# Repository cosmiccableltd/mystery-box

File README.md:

# Mystery Box

## About
The Mystery Box is a small PCB which provides power ports for various devices to indicate a ringing phone and drive POE devices.
It was designed by [Cosmic Cable Ltd.](http://cosmic.cable.limited) to be used for self-made telephone booths. 

## Ports
| Port Name | Function                                                      | Usage                                   |
| --------- | --------                                                      | -----                                   |
| J1        | [POE](https://en.wikipedia.org/wiki/Power_over_Ethernet) Port | POE powered network device              |
| J2        | LAN Port                                                      | Connection to external network          |
| J3        | Analogue Telephone Port                                       | Connection to external analogue network |
| J4        | Analogue Telephone Port                                       | Connection to analogue telephone        |
| X1-1      | +12V                                                          |                                         |
| X1-2      |  GND (switched)                                               | swichted on ringing phone line          |
| X1-3      | +12V                                                          |                                         |
| X1-4      |  GND                                                          |                                         |
| X1-5      | +12V                                                          |                                         |
| X1-6      |  GND                                                          |                                         |
| X1-7      | +12V                                                          |                                         |
| X1-8      |  GND                                                          |                                         |

## Known Issues
We experienced that the PMV20EN Q2 Mosfet might die from to high current.
It should be changed to something which can handle more current or otherwise it must be ensured that the outgoing power is limited.

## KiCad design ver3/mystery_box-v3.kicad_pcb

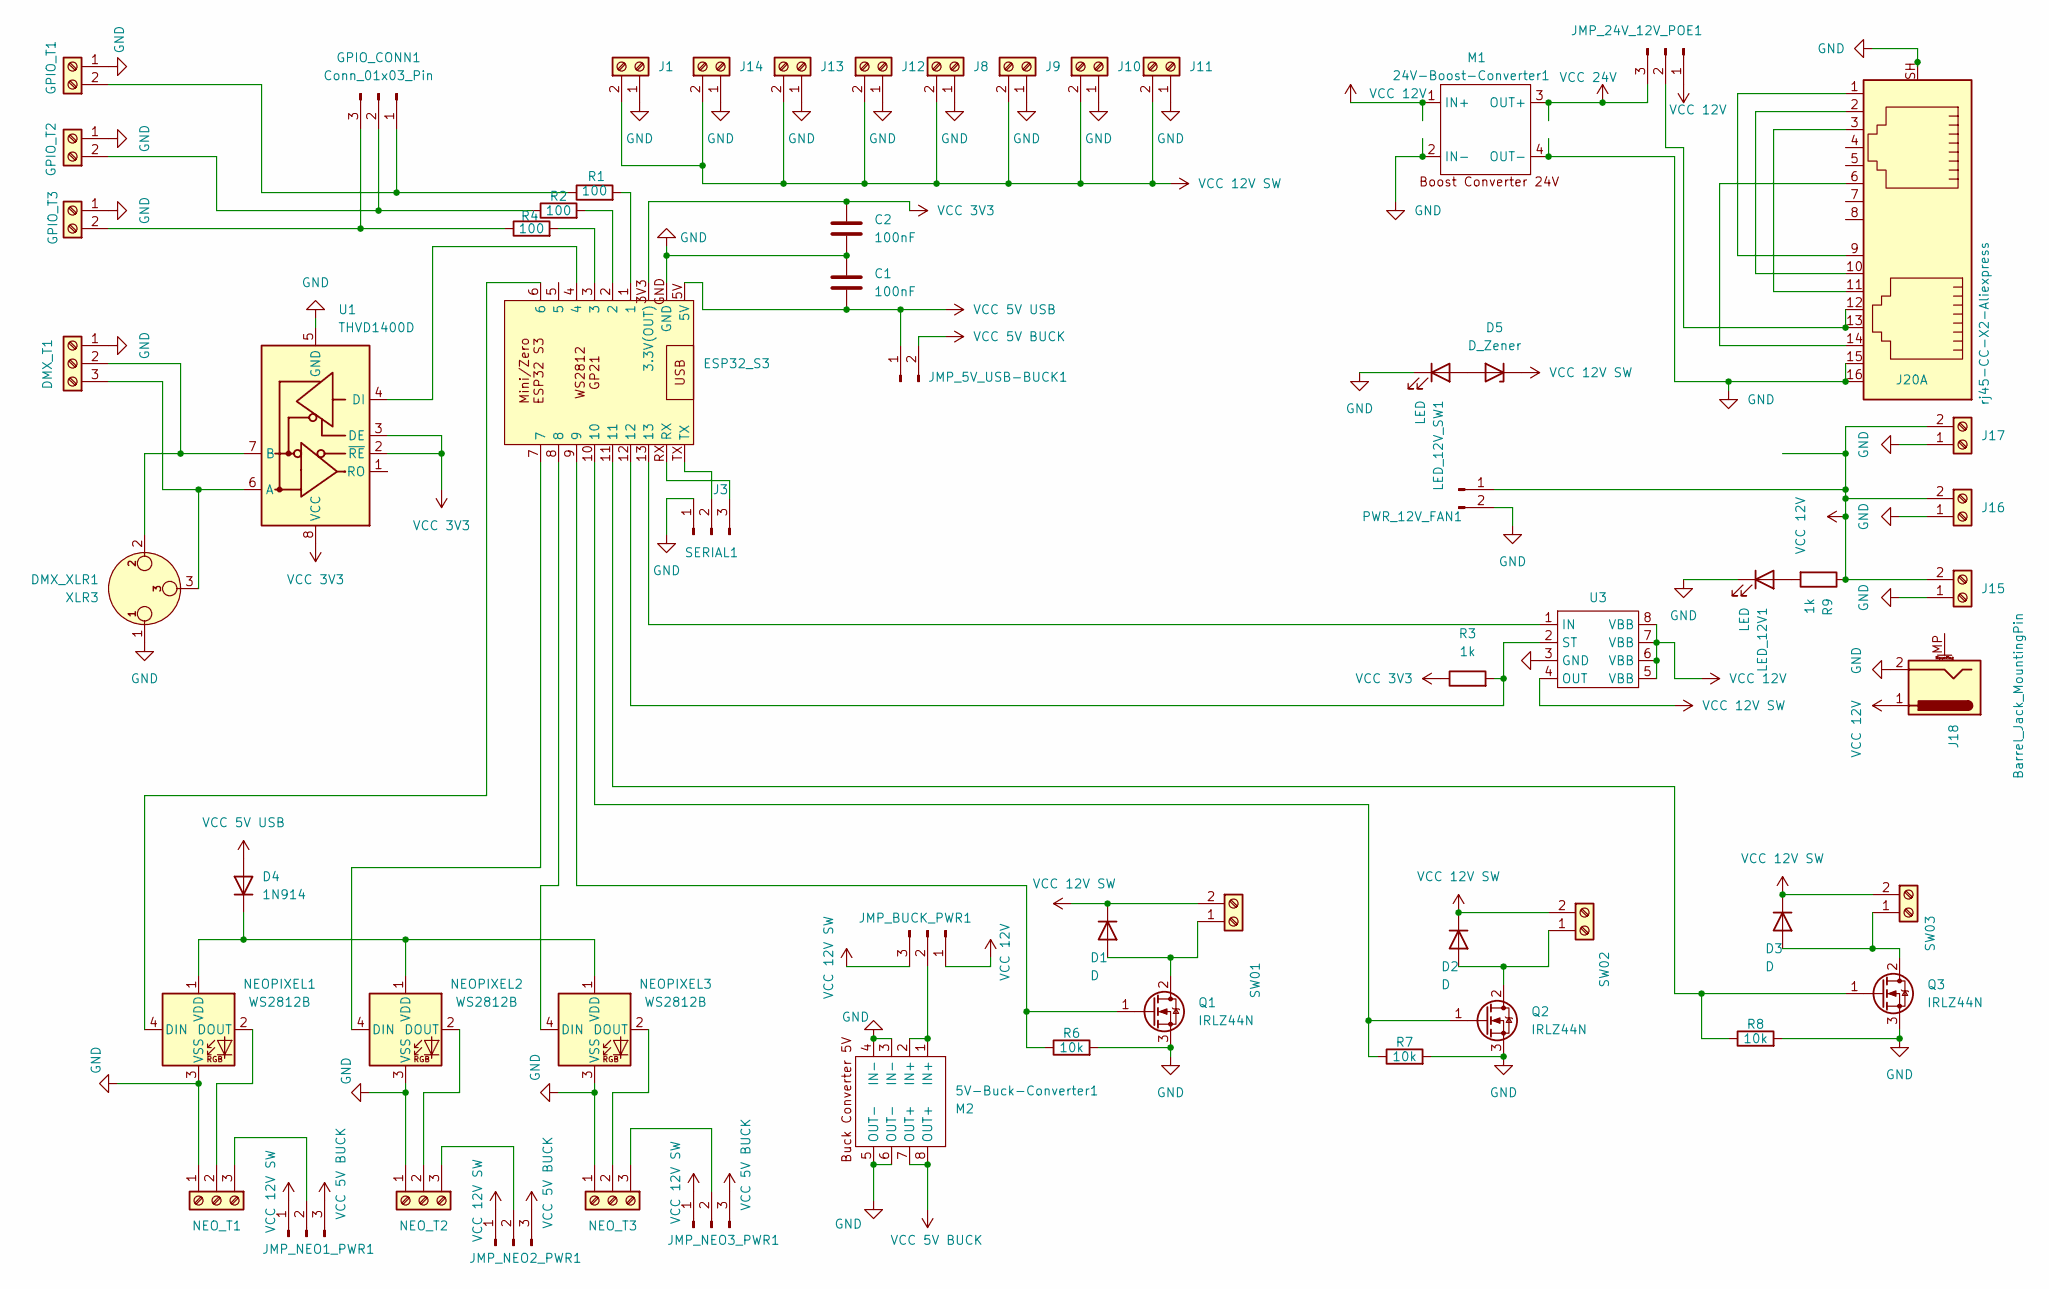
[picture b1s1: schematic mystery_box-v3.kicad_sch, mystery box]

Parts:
5V-Buck-Converter1: M2; 5V Buck Converter
24V-Boost-Converter1: M1; 24V Boost Converter
C1, C2: 100nF; C_Rect_L7.0mm_W2.5mm_P5.00mm
D1, D2, D3: D; D_DO-15_P10.16mm_Horizontal
D4: 1N914; D_DO-35_SOD27_P7.62mm_Horizontal
D5: D_Zener; D_A-405_P7.62mm_Horizontal
DMX_T1: Screw_Terminal_01x03; TerminalBlock_MaiXu_MX126-5.0-03P_1x03_P5.00mm
DMX_XLR1: XLR3; Jack_XLR_Neutrik_NC3FAAH-0_Horizontal
ESP32_S3: ESP32-S3-Zero
GPIO_CONN1: Conn_01x03_Pin; PinHeader_1x03_P2.54mm_Vertical
GPIO_T1, GPIO_T2, GPIO_T3: Screw_Terminal_01x02; TerminalBlock_MaiXu_MX126-5.0-02P_1x02_P5.00mm
J1, J8, J9, J10, J11, J12, J13, J14, J15, J16, J17: Screw_Terminal_01x02; TerminalBlock_MaiXu_MX126-5.0-02P_1x02_P5.00mm
J3: SERIAL1; PinHeader_1x03_P2.54mm_Vertical
J18: Barrel_Jack_MountingPin; CUI_PJ-050BH
J20: rj45-CC-X2-Aliexpress; RJ45_X2_CC_Aliexpress
JMP_5V_USB-BUCK1: Conn_01x02_Pin; PinHeader_1x02_P2.54mm_Vertical
JMP_24V_12V_POE1: Conn_01x03_Pin; PinHeader_1x03_P2.54mm_Vertical
JMP_BUCK_PWR1: Conn_01x03_Pin; PinHeader_1x03_P2.54mm_Vertical
JMP_NEO1_PWR1, JMP_NEO2_PWR1, JMP_NEO3_PWR1: Conn_01x03_Pin; PinHeader_1x03_P2.54mm_Vertical
LED_12V1, LED_12V_SW1: LED; LED_D3.0mm_Horizontal_O1.27mm_Z2.0mm_Clear
NEOPIXEL1, NEOPIXEL2, NEOPIXEL3: WS2812B; LED_WS2812B_PLCC4_5.0x5.0mm_P3.2mm
NEO_T1, NEO_T2, NEO_T3: Screw_Terminal_01x03; TerminalBlock_MaiXu_MX126-5.0-03P_1x03_P5.00mm
PWR_12V_FAN1: Conn_01x02_Pin; PinHeader_1x02_P2.54mm_Vertical
Q1, Q2, Q3: IRLZ44N; TO-220-3_Vertical
R1, R2, R4: 100; R_Axial_DIN0207_L6.3mm_D2.5mm_P10.16mm_Horizontal
R3, R9: 1k; R_Axial_DIN0207_L6.3mm_D2.5mm_P10.16mm_Horizontal
R6, R7, R8: 10k; R_Axial_DIN0207_L6.3mm_D2.5mm_P10.16mm_Horizontal
SW01, SW02, SW03: Screw_Terminal_01x02; TerminalBlock_MaiXu_MX126-5.0-02P_1x02_P5.00mm
SmartSwitch1: U3; SOIC-8_3.9x4.9mm_P1.27mm
U1: THVD1400D; SOIC-8_3.9x4.9mm_P1.27mm

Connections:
GND: 5V-Buck-Converter1.3 (IN-), 5V-Buck-Converter1.4 (IN-), 5V-Buck-Converter1.5 (OUT-), 5V-Buck-Converter1.6 (OUT-), 24V-Boost-Converter1.2 (IN-), 24V-Boost-Converter1.4 (OUT-), C1.1, C2.2, DMX_T1.1 (Pin_3), DMX_XLR1.1, ESP32_S3.GND, GPIO_T1.1 (Pin_2), GPIO_T2.1 (Pin_2), GPIO_T3.1 (Pin_2), J1.1 (Pin_2), J3.1, J8.1 (Pin_2), J9.1 (Pin_2), J10.1 (Pin_2), J11.1 (Pin_2), J12.1 (Pin_2), J13.1 (Pin_2), J14.1 (Pin_2), J15.1 (Pin_2), J16.1 (Pin_2), J17.1 (Pin_2), J18.2, J20.15, J20.16, J20.SH, LED_12V1.1 (K), LED_12V_SW1.1 (K), NEOPIXEL1.3 (VSS), NEOPIXEL2.3 (VSS), NEOPIXEL3.3 (VSS), NEO_T1.1 (Pin_3), NEO_T2.1 (Pin_3), NEO_T3.1 (Pin_3), PWR_12V_FAN1.2, Q1.3 (S), Q2.3 (S), Q3.3 (S), R6.2, R7.2, R8.2, SmartSwitch1.3 (GND), U1.5 (GND)
unnamed: D1.2 (A), Q1.2 (D), SW01.1 (Pin_2)
unnamed: D2.2 (A), Q2.2 (D), SW02.1 (Pin_2)
unnamed: D3.2 (A), Q3.2 (D), SW03.1 (Pin_2)
unnamed: D4.1 (K), NEOPIXEL1.1 (VDD), NEOPIXEL2.1 (VDD), NEOPIXEL3.1 (VDD)
unnamed: D5.2 (A), LED_12V_SW1.2 (A)
unnamed: DMX_T1.3 (Pin_1), DMX_XLR1.3, U1.6 (A)
unnamed: DMX_T1.2, DMX_XLR1.2, U1.7 (B)
unnamed: ESP32_S3.1, R1.2
unnamed: ESP32_S3.2, R2.2
unnamed: ESP32_S3.3, R4.2
unnamed: GPIO_CONN1.1, GPIO_T1.2 (Pin_1), R1.1
unnamed: GPIO_CONN1.2, GPIO_T2.2 (Pin_1), R2.1
unnamed: GPIO_CONN1.3, GPIO_T3.2 (Pin_1), R4.1
unnamed: ESP32_S3.TX, J3.2
unnamed: ESP32_S3.RX, J3.3
unnamed: J20.1, J20.9
unnamed: J20.2, J20.10
unnamed: J20.3, J20.11
unnamed: J20.6, J20.14
unnamed 20: J20.12, J20.13, JMP_24V_12V_POE1.2; also elsewhere on the board
unnamed: 5V-Buck-Converter1.1 (IN+), 5V-Buck-Converter1.2 (IN+), JMP_BUCK_PWR1.2
unnamed: JMP_NEO1_PWR1.2, NEO_T1.3 (Pin_1)
unnamed: JMP_NEO2_PWR1.2, NEO_T2.3 (Pin_1)
unnamed: JMP_NEO3_PWR1.2, NEO_T3.3 (Pin_1)
unnamed: LED_12V1.2 (A), R9.2
unnamed: ESP32_S3.6, NEOPIXEL1.4 (DIN)
unnamed: NEOPIXEL1.2 (DOUT), NEO_T1.2
unnamed: ESP32_S3.7, NEOPIXEL2.4 (DIN)
unnamed: NEOPIXEL2.2 (DOUT), NEO_T2.2
unnamed: ESP32_S3.8, NEOPIXEL3.4 (DIN)
unnamed: NEOPIXEL3.2 (DOUT), NEO_T3.2
unnamed: ESP32_S3.9, Q1.1 (G), R6.1
unnamed: ESP32_S3.10, Q2.1 (G), R7.1
unnamed: ESP32_S3.11, Q3.1 (G), R8.1
unnamed: ESP32_S3.13, SmartSwitch1.1 (IN)
unnamed: ESP32_S3.12, R3.2, SmartSwitch1.2 (ST)
unnamed: ESP32_S3.4, U1.4 (DI)
VCC 3V3: C2.1, ESP32_S3.3V3 (3.3V(OUT)), R3.1, U1.2 (~RE), U1.3 (DE), U1.8 (VCC)
VCC 5V BUCK: 5V-Buck-Converter1.7 (OUT+), 5V-Buck-Converter1.8 (OUT+), JMP_5V_USB-BUCK1.2, JMP_NEO1_PWR1.3, JMP_NEO2_PWR1.3, JMP_NEO3_PWR1.3
VCC 5V USB: C1.2, D4.2 (A), ESP32_S3.5V, JMP_5V_USB-BUCK1.1
VCC 12V: 24V-Boost-Converter1.1 (IN+), J15.2 (Pin_1), J16.2 (Pin_1), J17.2 (Pin_1), J18.1, JMP_24V_12V_POE1.1, JMP_BUCK_PWR1.1, PWR_12V_FAN1.1, R9.1, SmartSwitch1.5 (VBB), SmartSwitch1.6 (VBB), SmartSwitch1.7 (VBB), SmartSwitch1.8 (VBB); also elsewhere on the board
VCC 12V SW: D1.1 (K), D2.1 (K), D3.1 (K), D5.1 (K), J1.2 (Pin_1), J8.2 (Pin_1), J9.2 (Pin_1), J10.2 (Pin_1), J11.2 (Pin_1), J12.2 (Pin_1), J13.2 (Pin_1), J14.2 (Pin_1), JMP_BUCK_PWR1.3, JMP_NEO1_PWR1.1, JMP_NEO2_PWR1.1, JMP_NEO3_PWR1.1, SW01.2 (Pin_1), SW02.2 (Pin_1), SW03.2 (Pin_1), SmartSwitch1.4 (OUT)
VCC 24V: 24V-Boost-Converter1.3 (OUT+), JMP_24V_12V_POE1.3; also elsewhere on the board

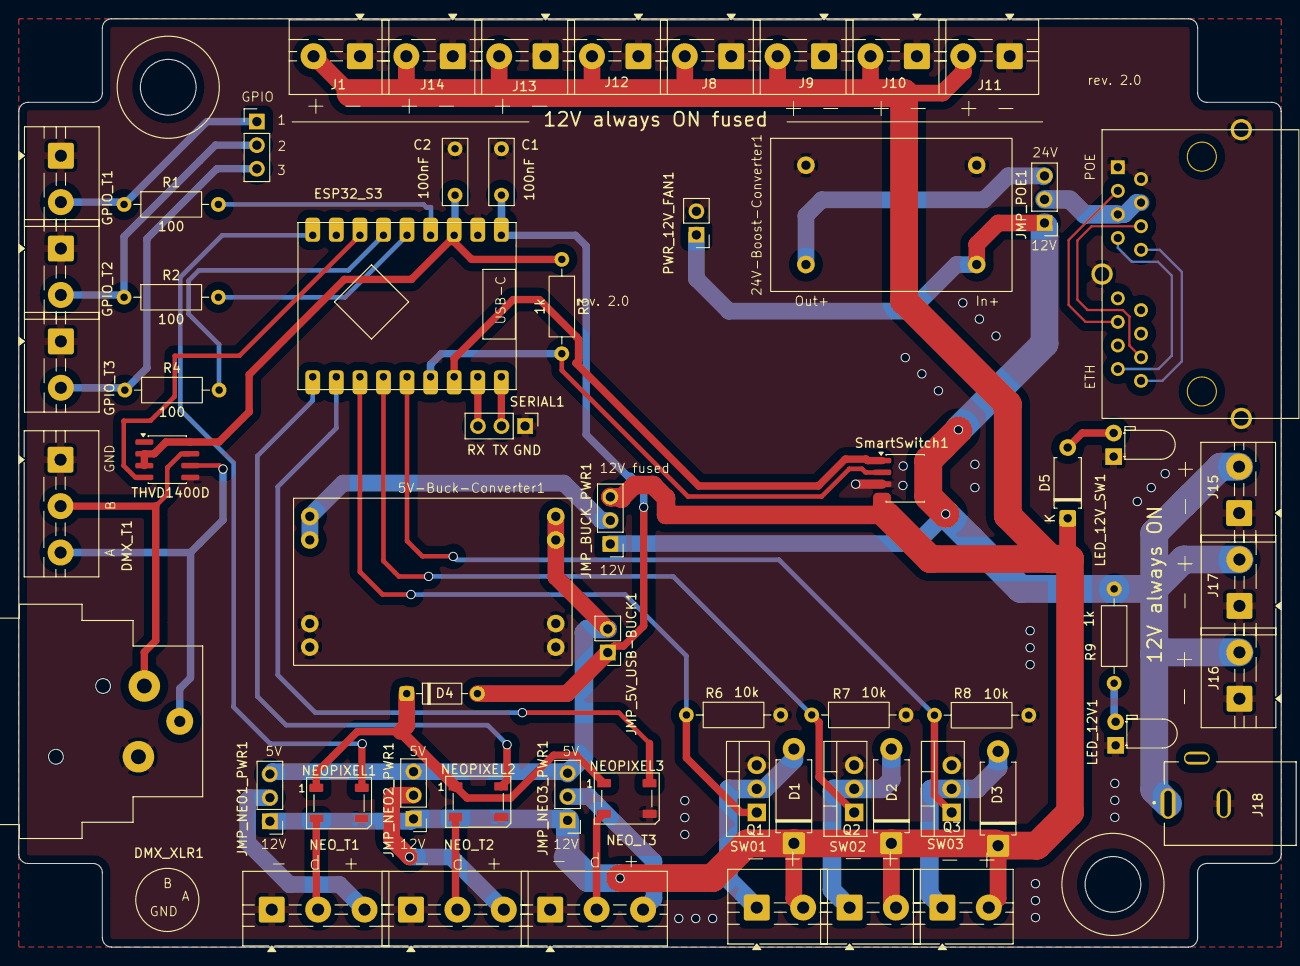
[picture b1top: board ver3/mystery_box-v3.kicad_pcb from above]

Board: 2 copper layers, 136.0 x 100.0 mm, 61 parts (0 on the bottom side), 44 nets.

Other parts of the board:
JMP_POE1: Conn_01x03_Pin; PinHeader_1x03_P2.54mm_Vertical

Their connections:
unnamed 20: JMP_POE1.2; also elsewhere on the board
VCC 12V: JMP_POE1.1; also elsewhere on the board
VCC 24V: JMP_POE1.3; also elsewhere on the board

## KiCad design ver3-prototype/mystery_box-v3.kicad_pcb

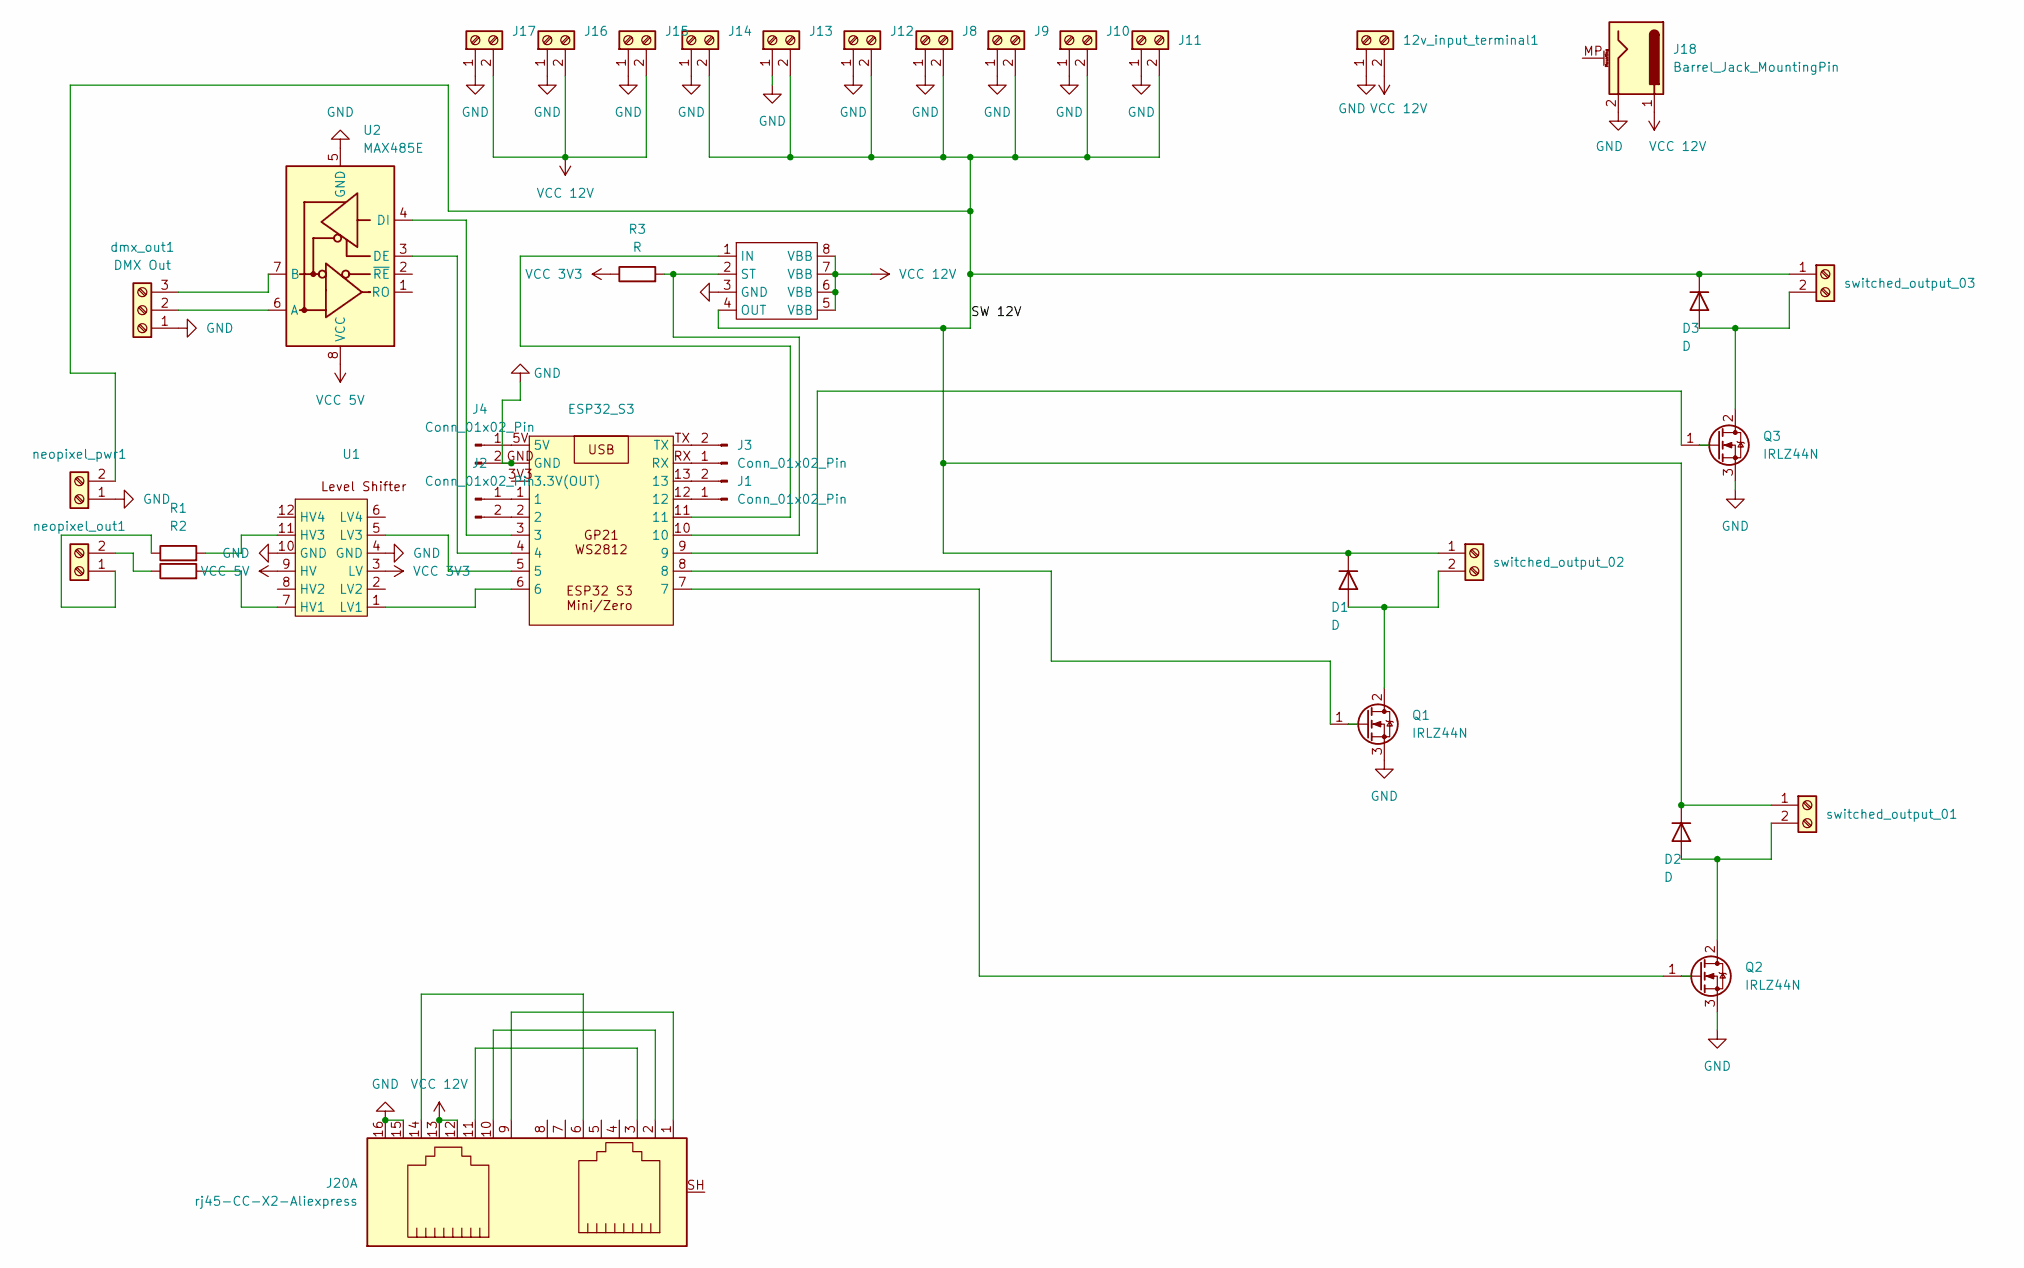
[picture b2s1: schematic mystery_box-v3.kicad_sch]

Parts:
12v_input_terminal1: Screw_Terminal_01x02; TerminalBlock_MaiXu_MX126-5.0-02P_1x02_P5.00mm
D1, D2, D3: D; D_DO-15_P10.16mm_Horizontal
ESP32_S3: ESP32-S3-Zero
J1, J2, J3, J4: Conn_01x02_Pin; PinHeader_1x02_P1.00mm_Vertical
J8, J9, J10, J11, J12, J13, J14, J15, J16, J17: Screw_Terminal_01x02; TerminalBlock_MaiXu_MX126-5.0-02P_1x02_P5.00mm
J18: Barrel_Jack_MountingPin; CUI_PJ-050BH
J20: rj45-CC-X2-Aliexpress; RJ45_X2_CC_Aliexpress
Q1, Q2, Q3: IRLZ44N; TO-220-3_Vertical
R1, R2, R3: R; R_Axial_DIN0207_L6.3mm_D2.5mm_P10.16mm_Horizontal
U1: level_shifter
U2: MAX485E; max845 modul
U3: SOIC-8_3.9x4.9mm_P1.27mm
dmx_out1: DMX Out; TerminalBlock_MaiXu_MX126-5.0-03P_1x03_P5.00mm
neopixel_out1: Screw_Terminal_01x02; TerminalBlock_MaiXu_MX126-5.0-02P_1x02_P5.00mm
neopixel_pwr1: Screw_Terminal_01x02; TerminalBlock_MaiXu_MX126-5.0-02P_1x02_P5.00mm
switched_output_01, switched_output_02, switched_output_03: Screw_Terminal_01x02; TerminalBlock_MaiXu_MX126-5.0-02P_1x02_P5.00mm

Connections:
/SW 12V: D1.1 (K), D2.1 (K), D3.1 (K), J8.2, J9.2, J10.2, J11.2, J12.2, J13.2, J14.2, U3.4 (OUT), neopixel_pwr1.2, switched_output_01.1, switched_output_02.1, switched_output_03.1; also elsewhere on the board
GND: 12v_input_terminal1.1, ESP32_S3.GND, J4.2, J8.1, J9.1, J10.1, J11.1, J12.1, J13.1, J14.1, J15.1, J16.1, J17.1, J18.2, J20.15, J20.16, Q1.3 (S), Q2.3 (S), Q3.3 (S), U1.4 (GND), U1.10 (GND), U2.5 (GND), U3.3 (GND), dmx_out1.1, neopixel_pwr1.1; also elsewhere on the board
unnamed: D1.2 (A), Q1.2 (D), switched_output_02.2
unnamed: D2.2 (A), Q2.2 (D), switched_output_01.2
unnamed: D3.2 (A), Q3.2 (D), switched_output_03.2
unnamed: ESP32_S3.12, J1.1
unnamed: ESP32_S3.13, J1.2
unnamed: ESP32_S3.1, J2.1
unnamed: ESP32_S3.2, J2.2
unnamed: ESP32_S3.RX, J3.1
unnamed: ESP32_S3.TX, J3.2
unnamed: ESP32_S3.5V, J4.1
unnamed: J20.1, J20.9
unnamed: J20.2, J20.10
unnamed: J20.3, J20.11
unnamed: J20.6, J20.14
unnamed: ESP32_S3.8, Q1.1 (G)
unnamed: ESP32_S3.7, Q2.1 (G)
unnamed: ESP32_S3.9, Q3.1 (G)
unnamed: R2.2, U1.7 (HV1)
unnamed: R1.2, U1.11 (HV3)
unnamed: ESP32_S3.6, U1.1 (LV1)
unnamed: ESP32_S3.5, U1.5 (LV3)
unnamed: U2.6 (A), dmx_out1.2
unnamed: U2.7 (B), dmx_out1.3
unnamed: ESP32_S3.4, U2.3 (DE)
unnamed: ESP32_S3.3, U2.4 (DI)
unnamed: ESP32_S3.11, U3.1 (IN)
unnamed: ESP32_S3.10, R3.2, U3.2 (ST)
unnamed: R1.1, neopixel_out1.1
unnamed: R2.1, neopixel_out1.2
VCC 3V3: R3.1, U1.3 (LV)
VCC 5V: U1.9 (HV), U2.8 (VCC)
VCC 12V: 12v_input_terminal1.2, J15.2, J16.2, J17.2, J18.1, J20.12, J20.13, U3.5 (VBB), U3.6 (VBB), U3.7 (VBB), U3.8 (VBB)

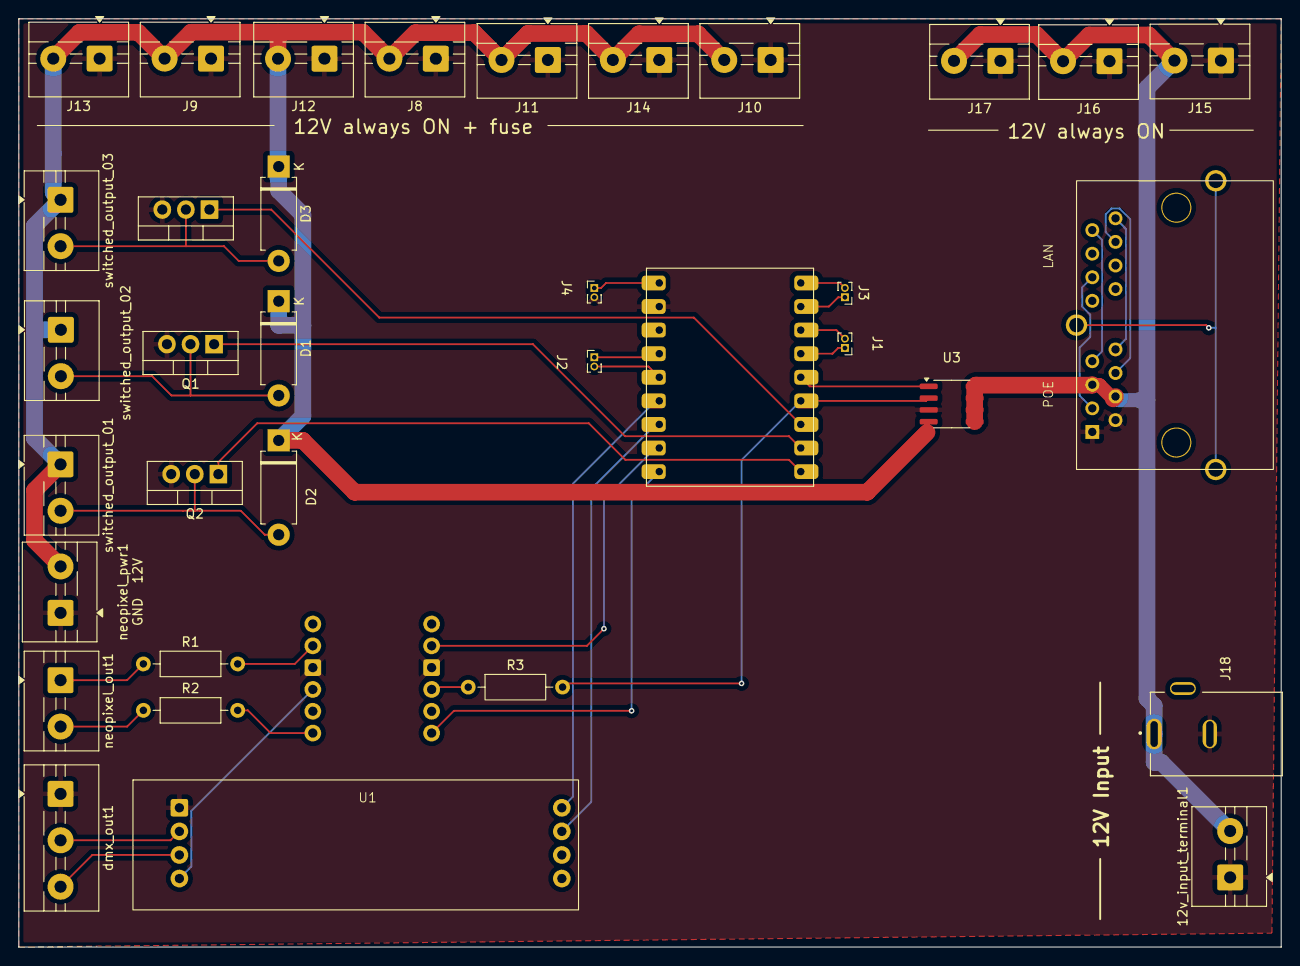
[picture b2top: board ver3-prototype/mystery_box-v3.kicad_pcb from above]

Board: 2 copper layers, 136.0 x 100.0 mm, 36 parts (0 on the bottom side), 34 nets.

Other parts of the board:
neopixel_pwr1
GND  12V: Screw_Terminal_01x02; TerminalBlock_MaiXu_MX126-5.0-02P_1x02_P5.00mm

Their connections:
/SW 12V: neopixel_pwr1 GND 12V.2; also elsewhere on the board
GND: neopixel_pwr1 GND 12V.1; also elsewhere on the board

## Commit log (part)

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2022-08-31 initial release
2022-09-01 added ver1
2022-09-01 added ver2
2022-09-01 added overview.png
2023-03-05 added ver2 pictures
2025-02-25 added first draft v3
2025-02-25 first draft v3
2025-03-05 update 2. meeting
2025-03-27 Added current PDF
2025-03-27 removed test pdf
2025-03-27 added pipeline for PDF creation
2025-04-15 added footprints for rj45, max485 module
2025-04-15 kikad symbol and footprint libraries
2025-05-06 pcb editor beginning
2025-05-07 added pcd to pdf pipeline
2025-05-07 enabled pipeline for pcb
2025-05-20 smart switch
2025-05-27 final prototype v3
2025-05-29 added notes
2025-11-05 first edit of serious ver3
2025-11-18 schematic with converter + footprints
2025-11-25 renamed ver3-prototype
2025-11-25 beginning ver3 PCB
2025-12-02 ver3: first PCB layout
2025-12-02 readded DMX
2026-01-13 beginning ver3 PCB routing
2026-02-04 v3: first draft finished
2026-02-04 ver3: all layers visible
2026-02-10 logo + silk stuff
2026-02-17 ver3: added GND to serial1
2026-02-17 ver3: gitignore zip backups
2026-02-17 ver3: RJ45 data routing on same side
2026-02-18 ver3: silkscreen beaty & 12v fused LED
2026-02-25 updated BOM
2026-02-25 ver3: fab outputs
2026-02-25 removed old stuff
2026-02-25 added BOM
2026-02-25 fixed SmartSwitch Pad
2026-02-25 mounting holes rework
2026-04-02 ver3: found some bauteile
2026-05-10 leftover changes
2026-05-10 added file
